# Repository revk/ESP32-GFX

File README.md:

# Simple SPI display controller

Provides simple tools to allow a screen buffer to be updated with text, boxes, etc.

Handles basic RGB for OLED/LCD RGB display, and simple mono for epaper.

Designed to allow for various SPI based display devices to be selected as part of config.

Note that the current state, graphics buffer, etc, are global, so only one display is supported.

- Includes scaled vector based font based on SAA5050 5x9 (Teletext/MODE7) with anti-aliasing.
- Includes scaled 7 segment (plus `.` and `:`), with anti-aliasing
- Includes simple box and line drawing

## Display types

### Solid colour (e-paper)

Displays with simple solid colour, such as black/white, black/red/white, etc, are handled quite simply with each pixel being one of the solid colours. The colour picked simply mapper from the RGB specified.

A simple dithering is applied on grey levels.

Anti-aliasing and alpha blending are not supported (top bit of alpha determines if plotted of not). As such italics is not recommended (text and 7 segment).

### Greyscale and colour

Displays with greyscale or colours allow antialiasing and alpha blending. A pixel can be set based on an RGB value - for greyscale this is mapped to a grey level.

Alpha blending is handled, mixing the new plotted pixel with the existing based on an alpha level.

Antialiasing is used for text, and 7 segment digits to improve quality, this will be added to other functions (line, circle, etc).

### Key functions

#### `gfx_init`

Sets up the display and options including all GPIOs and a number of flags.

#### `gfx_width` / `gfx_height` / `gfx_bpp`

Provide details of current display size and attriblues

#### `gfx_lock` / `gfx_unlock`

Call lock, then plot things, then unlock. Depending on the initial settings the display will be updated on unlock or on a background task (which locks while sending).

#### `gfx_foreground`/`gfx_background`

These set the current foreground and background to use. For text and 7 segment a solid background is set as a box first and then the text or 7 segment is plotted. This can be disabled by setting the same colour for foreground and background allowing plotting over the existing pixels with alpha blending. You can check current values with `gfx_f` and `gfx_b`.

#### `gfx_pixel_argb`

This set a pixel based on a 32 bit value (AARRGGBB), an alpha of 0xFF is plot, 0x00 is don't plot, otherwise alpha blend (non antialiasing displays simply test top bit of alpha to plot or not plot).

- `gfx_pixel` plots using current foreground colour width specified alpha
- `gfx_pixel_bg` plots using current background colour width specified alpha
- `gfx_pixel_rgb` plots specified colour (RRGGBB), same as alpha 0xFF
- `gfx_clear` plots a blend of current background and current foreground for whole display based on an alpha value
- `gfx_pixel_fb` plots a blend of current background and current foreground for a pixel based on an alpha value (if background/foreground same then does `gfx_pixel`)

#### `gfx_pos`

Sets current position and alignment for other functions. You can get current values `gf_x`, `gfx_y`, `gfx_a`.

#### `gfx_text` and `gfx_7seg`

These plot text or fixed digits. They have a number of flags and a based size. It plots at current position and alignment and moves to new position.

- `gfx_text` plots vector based text including a load of unicode characters - this allows newlines
- `gfx_7seg` plots digits, and `.` or `:` after a digit, and a number of letters than can be expressed using 7 segment display format

You can check size of text with `gfx_text_size` and `gfx_7seg_size`.

Note for text, a `size` of 0 plots a non anti-aliased size 1.

If using the `GFX_7SEG_SMALL_DOT` flag, a trailing `C` or `F` character is superscript (for temperatures).

There are various options including italic, dotty, blocky, etc.

#### `gfx_line`

A number of extra functions exist - these are being updated and new functions added.

#### `gfx_message`

This is a simple generic message display, typically used with a `message` command in various apps. The argument is a string with some special cases. The message is displayed centred from the top down, as several lines where lines are broken using a `/` character.

Lines can start with some characters within `[` and `]`, these include colour characters, e.g. `R` for red. A second colour character setting the background. A digit or digits sets the text size. You can also set flags for text (`_` for descenders, `|` for thin, `/` for italic).

Note: gfx_message calls gfx_lock/unlock.

### Some simple data tables

- `sin256` a table of sin() for 90 degrees (0-255) giving value 0-255
- `circle256` a table of x for y for a quarter circle 0-255 giving value 0-255

### Images

You can make use of the `lwpng` library for processing a png and calling `gfx_pixel_argb`. If you want to access the frame buffer `gfx_raw_w`, `gfx_raw_h` and `gfx_raw_b` allow access to the raw buffer - you will need to decode pixel values depending on `gfx_bpp` if you want to make a png.

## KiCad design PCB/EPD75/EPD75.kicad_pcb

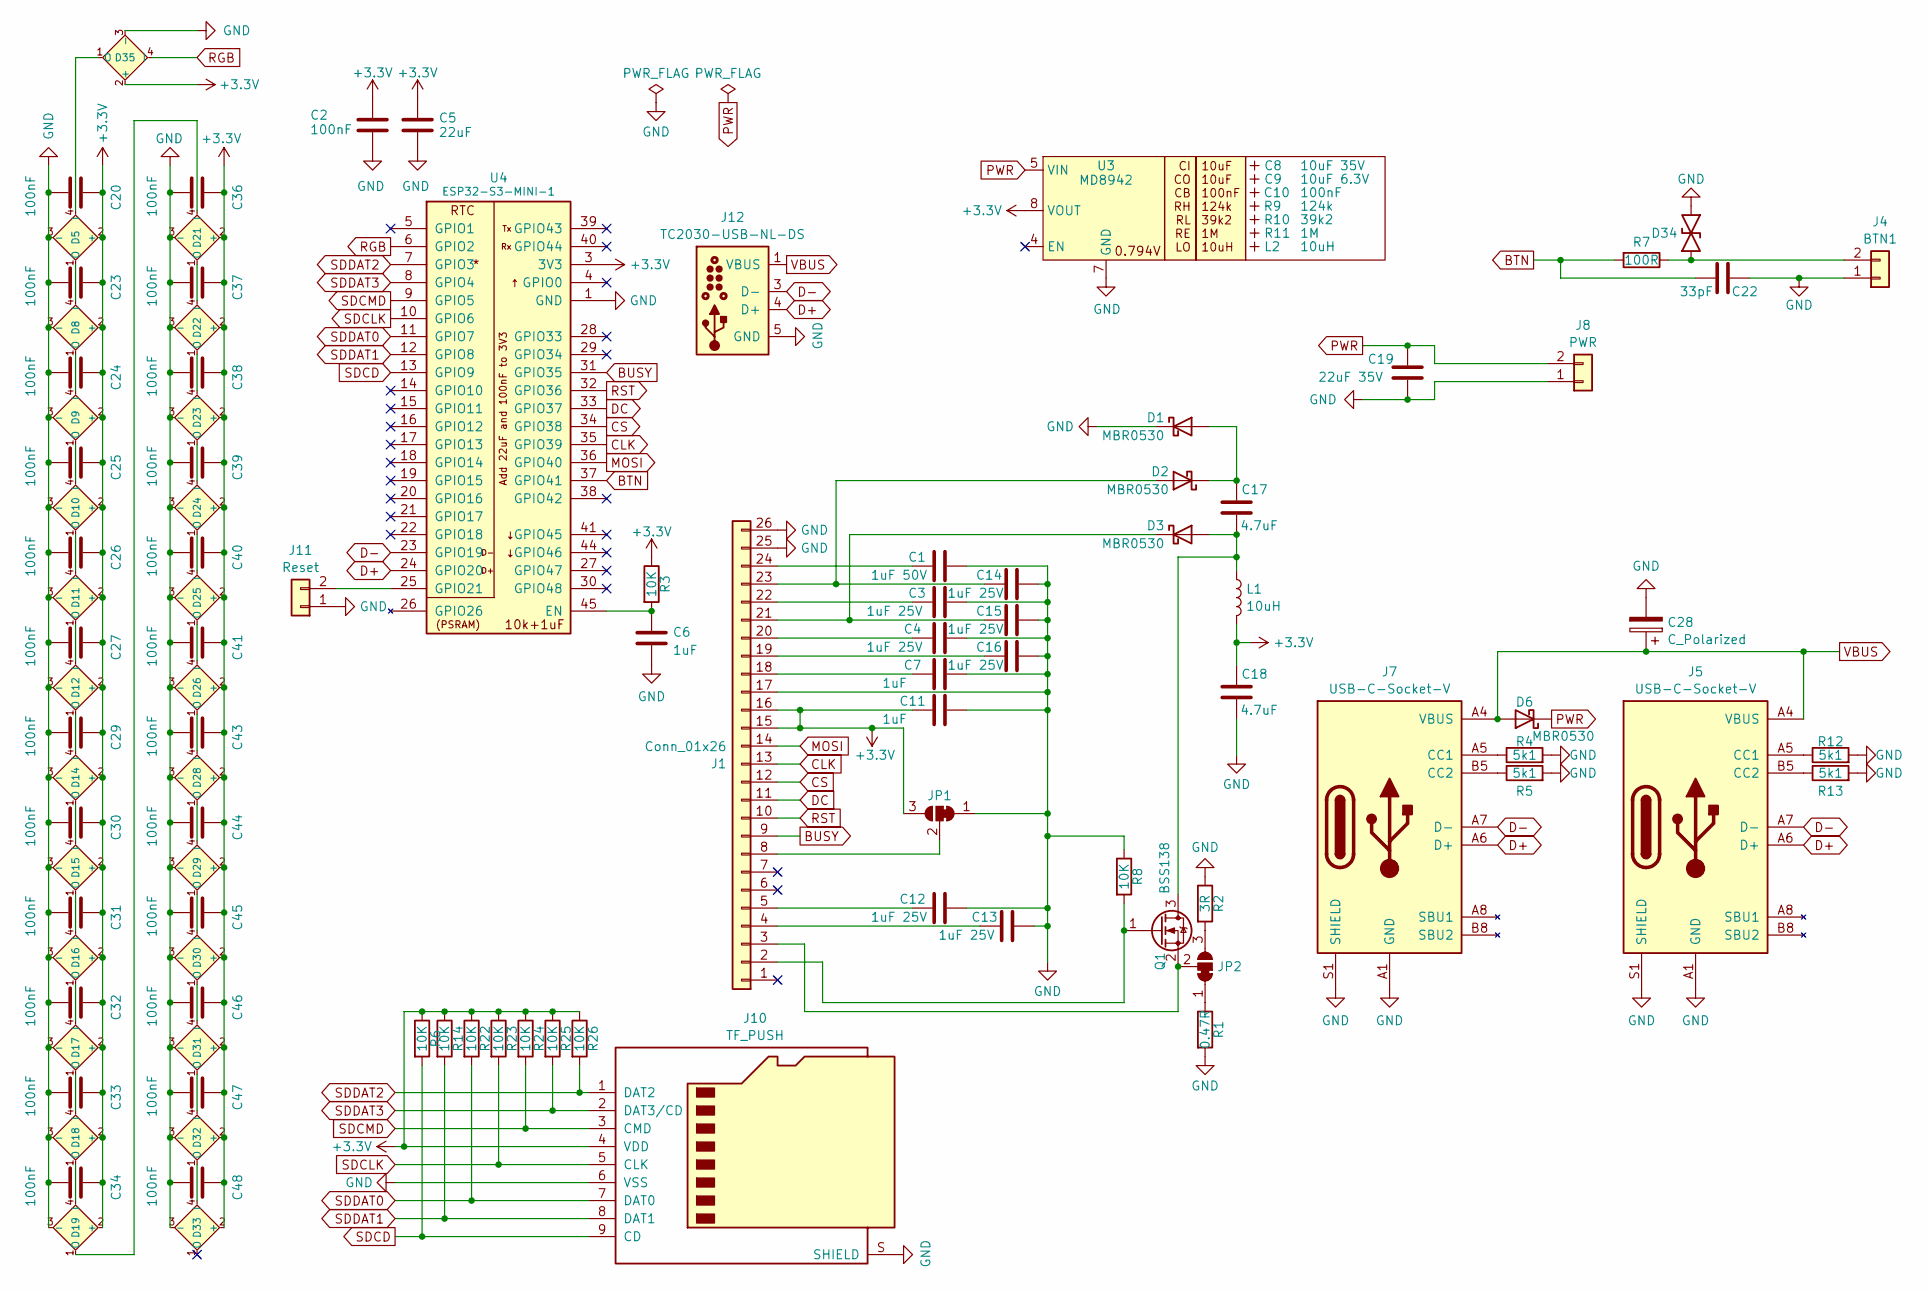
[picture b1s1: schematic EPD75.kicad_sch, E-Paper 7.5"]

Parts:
C1: 1uF 50V; C_0603
C2, C20, C23, C24, C25, C26, C27, C29, C30, C31, C32, C33, C34, C36, C37, C38, C39, C40, C41, C43, C44, C45, C46, C47, C48: 100nF; C_0402
C3, C4, C12, C13, C14, C15, C16: 1uF 25V; C_0402
C5: 22uF; C_0603
C6, C7, C11: 1uF; C_0402
C8: 10uF 35V; C_0603_; MPN C194427
C9: 10uF 6.3V; C_0603_; MPN C1691
C10: 100nF; C_0603_
C17, C18: 4.7uF; C_0402
C19: 22uF 35V; C_1210
C22: 33pF; C_0402
C28: C_Polarized; CP_EIA-7343-31_Kemet-D; MPN C106188
D1, D2, D3, D6: MBR0530; D_SOD-123; MPN C5204746
D5, D8, D9, D10, D11, D12, D14, D15, D16, D17, D18, D19, D21, D22, D23, D24, D25, D26, D28, D29, D30, D31, D32, D33, D35: XL-1010RGBC-WS2812B; MPN C5349953
D34: DFN1006-2L; MPN C5137770
J1: Conn_01x26; XUNPU-FPC-05FB-24PH20; MPN C2856831
J4: BTN1; WAGO-2060-452-998-404; MPN C2765055
J5, J7: USB-C-Socket-V; USB-C-Socket-H; MPN C709357
J8: PWR; WAGO-2060-452-998-404; MPN C2765055
J10: TF_PUSH; MPN C393941
J11: Reset; AA-Pad
J12: TC2030-USB-NL-DS; Tag-Connect_TC2030-IDC-NL_2x03_P1.27mm_Vertical
JP1, JP2: SolderJumper_3_Bridged12; SolderJumper3
L1: 10uH; L_4x4
L2: 10uH; L_4x4_
Q1: BSS138; SOT-23; MPN C2938375
R1: 0.47R; R_0402; MPN C2771738
R2: 3R; R_0402
R3, R6, R8, R14, R22, R23, R24, R25, R26: 10K; R_0402
R4, R5, R12, R13: 5k1; R_0402
R7: 100R; R_0402
R9: 124k; R_0402_; MPN C138062
R10: 39k2; R_0402_
R11: 1M; R_0402_
U3: MD8942; SOT-23-6-MD8942; MPN C2684786
U4: ESP32-S3-MINI-1; MPN C3013941

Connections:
+3.3V: C2.1, C5.1, C11.1, C18.2, C20.1, C23.1, C24.1, C25.1, C26.1, C27.1, C29.1, C30.1, C31.1, C32.1, C33.1, C34.1, C36.1, C37.1, C38.1, C39.1, C40.1, C41.1, C43.1, C44.1, C45.1, C46.1, C47.1, C48.1, D5.2 (+), D8.2 (+), D9.2 (+), D10.2 (+), D11.2 (+), D12.2 (+), D14.2 (+), D15.2 (+), D16.2 (+), D17.2 (+), D18.2 (+), D19.2 (+), D21.2 (+), D22.2 (+), D23.2 (+), D24.2 (+), D25.2 (+), D26.2 (+), D28.2 (+), D29.2 (+), D30.2 (+), D31.2 (+), D32.2 (+), D33.2 (+), D35.2 (+), J1.15, J1.16, J10.4 (VDD), JP1.3 (B), L1.2, R3.1, R6.1, R14.1, R22.1, R23.1, R24.1, R25.1, R26.1, U3.8 (VOUT), U4.3 (3V3)
BTN: C22.1, R7.2, U4.37 (GPIO41)
BUSY: J1.9, U4.31 (GPIO35)
CLK: J1.13, U4.35 (GPIO39)
CS: J1.12, U4.34 (GPIO38)
D+: J5.A6 (D+), J5.B6 (D+), J7.A6 (D+), J7.B6 (D+), J12.4 (D+), U4.24 (GPIO20)
D-: J5.A7 (D-), J5.B7 (D-), J7.A7 (D-), J7.B7 (D-), J12.3 (D-), U4.23 (GPIO19)
DC: J1.11, U4.33 (GPIO37)
GND: C1.2, C2.2, C3.2, C4.2, C5.2, C6.2, C7.2, C11.2, C12.2, C14.2, C15.2, C18.1, C19.2, C20.2, C22.2, C23.2, C24.2, C25.2, C26.2, C27.2, C28.2, C29.2, C30.2, C31.2, C32.2, C33.2, C34.2, C36.2, C37.2, C38.2, C39.2, C40.2, C41.2, C43.2, C44.2, C45.2, C46.2, C47.2, C48.2, D1.1 (K), D5.3 (-), D8.3 (-), D9.3 (-), D10.3 (-), D11.3 (-), D12.3 (-), D14.3 (-), D15.3 (-), D16.3 (-), D17.3 (-), D18.3 (-), D19.3 (-), D21.3 (-), D22.3 (-), D23.3 (-), D24.3 (-), D25.3 (-), D26.3 (-), D28.3 (-), D29.3 (-), D30.3 (-), D31.3 (-), D32.3 (-), D33.3 (-), D34.1, D35.3 (-), J1.17, J1.25, J1.26, J4.1, J5.A1 (GND), J5.A12 (GND), J5.B1 (GND), J5.B12 (GND), J5.S1 (SHIELD), J7.A1 (GND), J7.A12 (GND), J7.B1 (GND), J7.B12 (GND), J7.S1 (SHIELD), J8.1, J10.6 (VSS), J10.S (SHIELD), J11.1, J12.5 (GND), J12.6 (GND), JP1.1 (A), R1.2, R2.1, R4.2, R5.2, R8.1, R12.2, R13.2, U3.2 (GND), U3.7 (GND), U4.1 (GND), U4.2 (GND), U4.42 (GND), U4.43 (GND), U4.46 (GND), U4.47 (GND), U4.48 (GND), U4.49 (GND), U4.50 (GND), U4.51 (GND), U4.52 (GND), U4.53 (GND), U4.54 (GND), U4.55 (GND), U4.56 (GND), U4.57 (GND), U4.58 (GND), U4.59 (GND), U4.60 (GND), U4.61 (GND), U4.62 (GND), U4.63 (GND), U4.64 (GND), U4.65 (GND)
MOSI: J1.14, U4.36 (GPIO40)
unnamed: C17.2, D1.2 (A), D2.1 (K)
unnamed: C14.1, D2.2 (A), J1.23
unnamed: C17.1, D3.2 (A), L1.1, Q1.3 (D)
unnamed: C15.1, D3.1 (K), J1.21
unnamed: D5.1 (O), D8.4 (I)
unnamed: D8.1 (O), D9.4 (I)
unnamed: D9.1 (O), D10.4 (I)
unnamed: D10.1 (O), D11.4 (I)
unnamed: D11.1 (O), D12.4 (I)
unnamed: D12.1 (O), D14.4 (I)
unnamed: D14.1 (O), D15.4 (I)
unnamed: D15.1 (O), D16.4 (I)
unnamed: D16.1 (O), D17.4 (I)
unnamed: D17.1 (O), D18.4 (I)
unnamed: D18.1 (O), D19.4 (I)
unnamed: D19.1 (O), D21.4 (I)
unnamed: D21.1 (O), D22.4 (I)
unnamed: D22.1 (O), D23.4 (I)
unnamed: D23.1 (O), D24.4 (I)
unnamed: D24.1 (O), D25.4 (I)
unnamed: D25.1 (O), D26.4 (I)
unnamed: D26.1 (O), D28.4 (I)
unnamed: D28.1 (O), D29.4 (I)
unnamed: D29.1 (O), D30.4 (I)
unnamed: D30.1 (O), D31.4 (I)
unnamed: D31.1 (O), D32.4 (I)
unnamed: D32.1 (O), D33.4 (I)
unnamed: D5.4 (I), D35.1 (O)
unnamed: J1.2, Q1.1 (G), R8.2
unnamed: J1.3, JP2.2 (C), Q1.2 (S)
unnamed: C12.1, J1.5
unnamed: J1.8, JP1.2 (C)
unnamed: C7.1, J1.18
unnamed: C4.1, J1.20
unnamed: C1.1, J1.24
unnamed: D34.2, J4.2, R7.1
unnamed: J5.A5 (CC1), R12.1
unnamed: J5.B5 (CC2), R13.1
unnamed: J7.A5 (CC1), R4.1
unnamed: J7.B5 (CC2), R5.1
unnamed: J11.2, U4.25 (GPIO21)
unnamed: JP2.1 (A), R1.1
unnamed: JP2.3 (B), R2.2
unnamed: C6.1, R3.2, U4.45 (EN)
PWR: C19.1, D6.1 (K), J8.2, U3.5 (VIN)
RGB: D35.4 (I), U4.6 (GPIO2)
RST: J1.10, U4.32 (GPIO36)
SDCD: J10.9 (CD), R6.2, U4.13 (GPIO9)
SDCLK: J10.5 (CLK), R23.2, U4.10 (GPIO6)
SDCMD: J10.3 (CMD), R24.2, U4.9 (GPIO5)
SDDAT0: J10.7 (DAT0), R22.2, U4.11 (GPIO7)
SDDAT1: J10.8 (DAT1), R14.2, U4.12 (GPIO8)
SDDAT2: J10.1 (DAT2), R26.2, U4.7 (GPIO3)
SDDAT3: J10.2 (DAT3/CD), R25.2, U4.8 (GPIO4)
VBUS: C28.1, D6.2 (A), J5.A4 (VBUS), J5.A9 (VBUS), J5.B4 (VBUS), J5.B9 (VBUS), J7.A4 (VBUS), J7.A9 (VBUS), J7.B4 (VBUS), J7.B9 (VBUS), J12.1 (VBUS), J12.2 (VBUS)

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
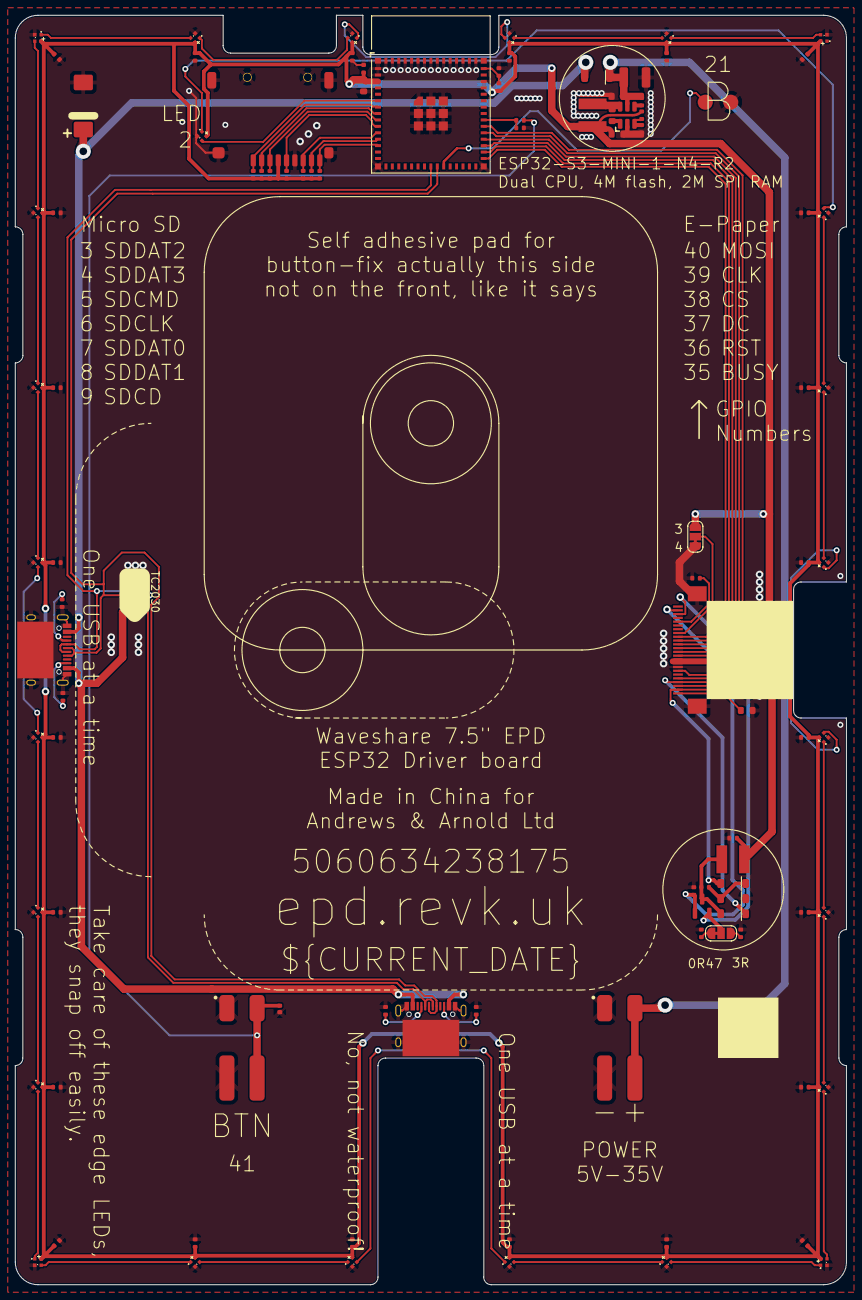
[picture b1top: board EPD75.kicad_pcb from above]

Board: 2 copper layers, 110.0 x 168.0 mm, 107 parts (0 on the bottom side), 66 nets.

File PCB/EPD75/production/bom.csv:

Designator,Footprint,Quantity,Value,LCSC Part #
C1,C_0603,1,1uF 50V,
C10,C_0603_,1,100nF,
"C11, C6, C7",C_0402,3,1uF,
"C12, C14, C15, C3, C4",C_0402,5,1uF 25V,
"C17, C18",C_0402,2,4.7uF,
C19,C_1210,1,22uF 35V,
"C2, C20, C23, C24, C25, C26, C27, C29, C30, C31, C32, C33, C34, C36, C37, C38, C39, C40, C41, C43, C44, C45, C46, C47, C48",C_0402,25,100nF,
C22,C_0402,1,33pF,
C28,CP_EIA-7343-31_Kemet-D,1,C_Polarized,C106188
C5,C_0603,1,22uF,
C8,C_0603_,1,10uF 35V,C194427
C9,C_0603_,1,10uF 6.3V,C1691
"D1, D2, D3, D6",D_SOD-123,4,MBR0530,C5204746
"D10, D11, D12, D14, D15, D16, D17, D18, D19, D21, D22, D23, D24, D25, D26, D28, D29, D30, D31, D32, D33, D35, D5, D8, D9",SMD1010,25,XL-1010RGBC-WS2812B,C5349953
D34,DFN1006-2L,1,~,C5137770
J1,XUNPU-FPC-05FB-24PH20,1,Conn_01x26,C2856831
J10,TF_PUSH,1,TF_PUSH,C393941
J4,WAGO-2060-452-998-404,1,BTN1,C2765055
"J5, J7",USB-C-Socket-H,2,USB-C-Socket-V,C709357
J8,WAGO-2060-452-998-404,1,PWR,C2765055
L1,L_4x4,1,10uH,
L2,L_4x4_,1,10uH,
Q1,SOT-23,1,BSS138,C2938375
R1,R_0402,1,0.47R,C2771738
R10,R_0402_,1,39k2,
R11,R_0402_,1,1M,
"R12, R13, R4, R5",R_0402,4,5k1,
"R14, R22, R23, R24, R25, R26, R3, R6, R8",R_0402,9,10K,
R2,R_0402,1,3R,
R7,R_0402,1,100R,
R9,R_0402_,1,124k,C138062
U3,SOT-23-6-MD8942,1,MD8942,C2684786
U4,ESP32-S3-MINI-1,1,ESP32-S3-MINI-1,C3013941

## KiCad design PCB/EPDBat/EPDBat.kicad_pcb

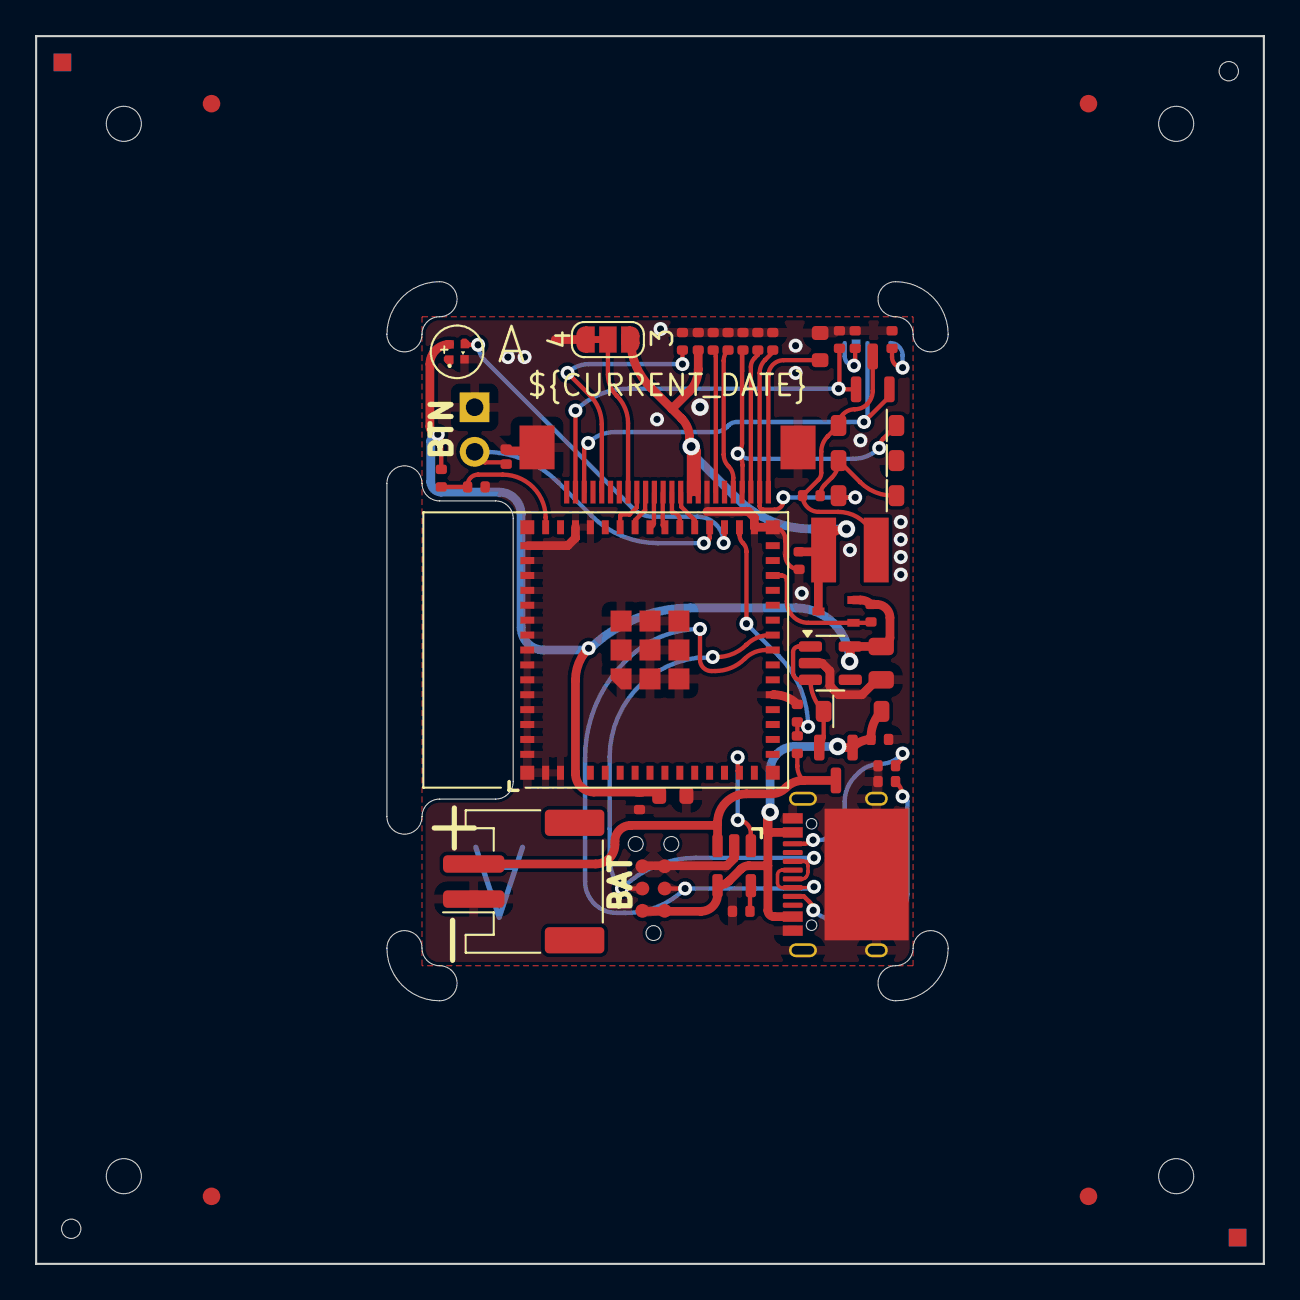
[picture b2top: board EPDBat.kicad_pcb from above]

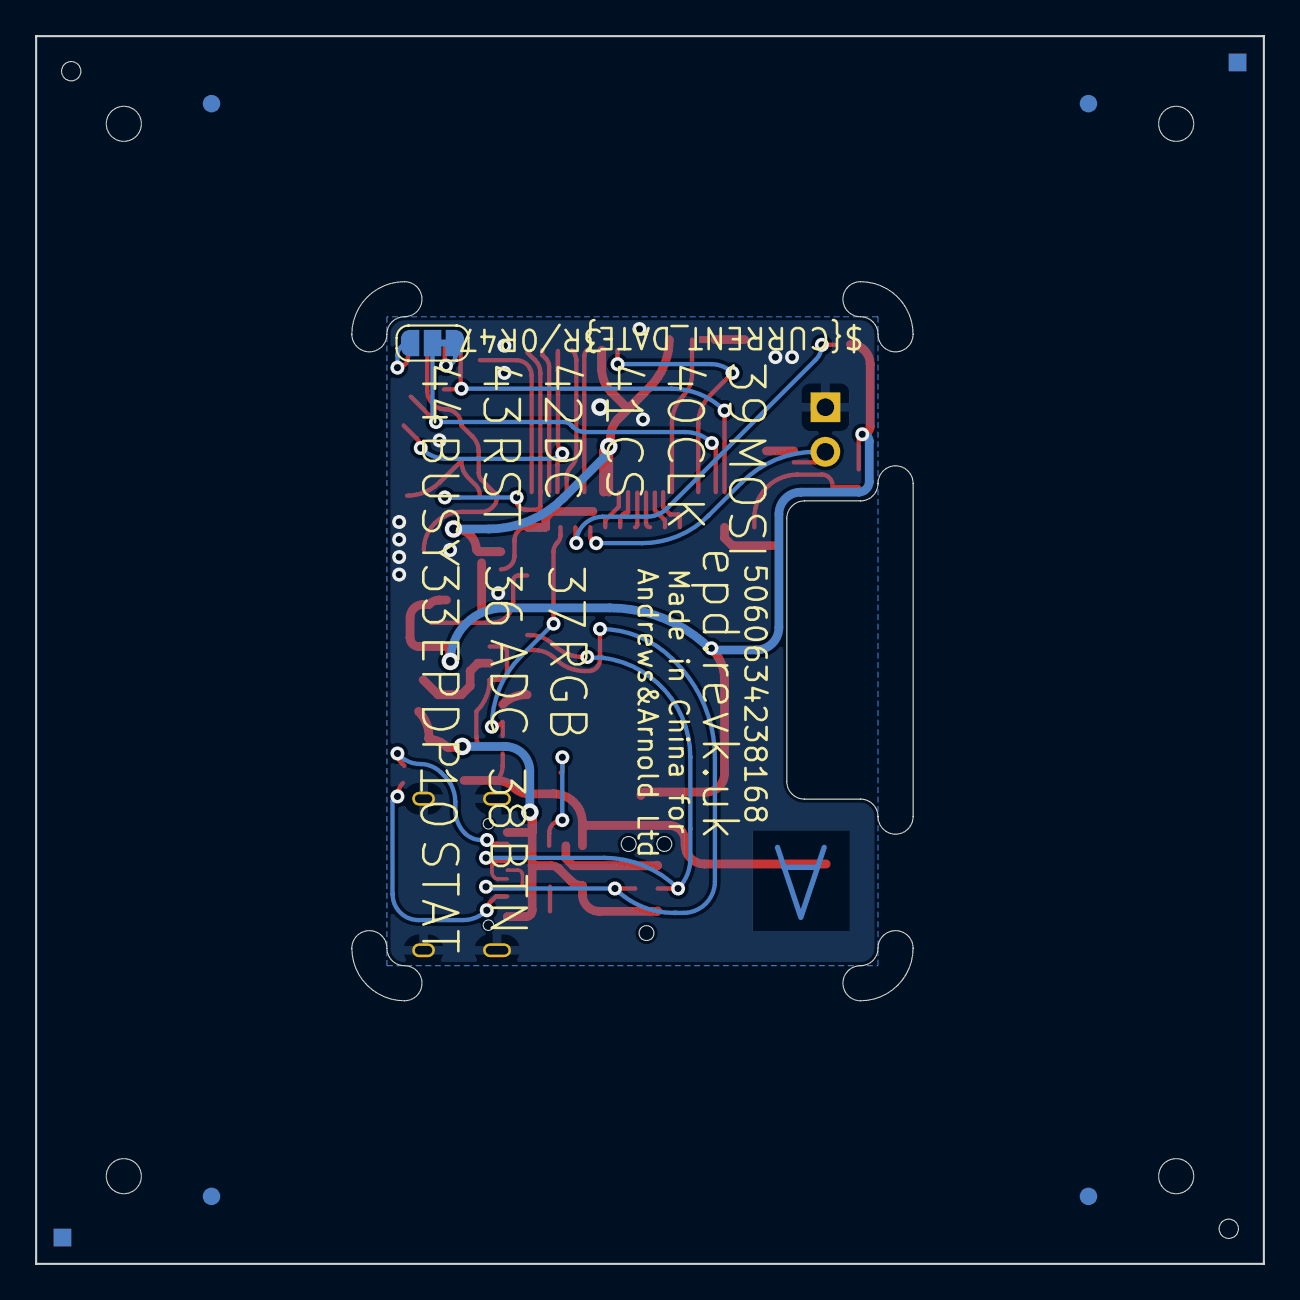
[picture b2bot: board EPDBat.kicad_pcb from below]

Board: 4 copper layers, 70.0 x 70.0 mm, 50 parts (3 on the bottom side), 37 nets.

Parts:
C1: 1uF 50V; C_0603
C2: 100nF; C_0402
C3, C4, C12, C14, C15: 1uF 25V; C_0402
C5: 22uF; C_0603
C6, C7, C11: 1uF; C_0402
C17, C18: 4.7uF; C_0402
C19: 4.7uF/50V; C_0805
D1, D2, D3, D5: MBR0530; D_SOD-123
D4: XL-1010RGBC-WS2812B; SMD1010
D6: DFN1006-2L
J1: Conn_01x26; XUNPU-FPC-05FB-24PH20
J4: Conn_01x02; PinHeader_1x02_P2.54mm_Vertical
J5: TC2030-USB-NL-DS; Tag-Connect_TC2030-IDC-NL_2x03_P1.27mm_Vertical
J7: USB-C-Socket-V; USB-C-Socket-H
J10: JST-PH-SM3-TB; JST_PH_S2B-PH-SM4-TB_1x02-1MP_P2.00mm_Horizontal
JP1, JP2: SolderJumper_3_Bridged12; SolderJumper3
L1: 10uH; L_4x4
PCB1: 70x70; PCB7070
Q1: BSS138; SOT-23
Q2: CJ2301; SOT-23
Q3: C179347; SOT-323_SC-70
R1: 0.47R; R_0402
R2: 3R; R_0402
R3, R8, R12, R13, R14: 10K; R_0402
R4, R5: 5k1; R_0402
R16, R17: 100K; R_0402
U1: TP4054; SOT-23-5
U2: ME6211C33M5G-N; SOT-23-5
U4: ESP32-S3-MINI-1
V1, V3, V4, V6: VCUT70N

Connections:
+3.3V: C2.1, C5.1, C19.1, D4.2 (+), Q3.2 (S), R3.1, R14.1, U2.5 (OUT), U4.3 (3V3)
ADC: R16.2, R17.1, U4.32 (GPIO36)
BTN: D6.2, J4.2, U4.34 (GPIO38)
BUSY: J1.9, U4.40 (GPIO44)
CLK: J1.13, U4.36 (GPIO40)
CS: J1.12, U4.37 (GPIO41)
D+: J5.4 (D+), J7.A6 (D+), J7.B6 (D+), U4.24 (GPIO20)
D-: J5.3 (D-), J7.A7 (D-), J7.B7 (D-), U4.23 (GPIO19)
DC: J1.11, U4.38 (GPIO42)
EPDP: Q3.1 (G), R14.2, U4.28 (GPIO33)
GND: C1.2, C2.2, C3.2, C4.2, C5.2, C6.2, C7.2, C11.2, C12.2, C14.2, C15.2, C18.1, C19.2, D1.1 (K), D4.3 (-), D6.1, J1.17, J1.25, J1.26, J4.1, J5.5 (GND), J5.6 (GND), J7.A1 (GND), J7.A12 (GND), J7.B1 (GND), J7.B12 (GND), J7.S1 (SHIELD), J10.1, JP2.1 (A), R1.2, R2.1, R4.2, R5.2, R8.1, R12.2, R13.1, R17.2, U1.2 (VSS), U2.2 (GND), U4.1 (GND), U4.2 (GND), U4.20 (GPIO16), U4.31 (GPIO35), U4.42 (GND), U4.43 (GND), U4.46 (GND), U4.47 (GND), U4.48 (GND), U4.49 (GND), U4.50 (GND), U4.51 (GND), U4.52 (GND), U4.53 (GND), U4.54 (GND), U4.55 (GND), U4.56 (GND), U4.57 (GND), U4.58 (GND), U4.59 (GND), U4.60 (GND), U4.61 (GND), U4.62 (GND), U4.63 (GND), U4.64 (GND), U4.65 (GND)
MOSI: J1.14, U4.35 (GPIO39)
unnamed: C17.2, D1.2 (A), D2.1 (K)
unnamed: C14.1, D2.2 (A), J1.23
unnamed: C17.1, D3.2 (A), L1.1, Q1.3 (D)
unnamed: C15.1, D3.1 (K), J1.21
unnamed: D5.1 (K), Q2.2 (S), U2.1 (IN), U2.3 (EN)
unnamed: J1.2, Q1.1 (G), R8.2
unnamed: J1.3, JP1.2 (C), Q1.2 (S)
unnamed: C12.1, J1.5
unnamed: J1.8, JP2.2 (C)
unnamed: C7.1, J1.18
unnamed: C4.1, J1.20
unnamed: C3.1, J1.22
unnamed: C1.1, J1.24
unnamed: J7.A5 (CC1), R4.1
unnamed: J7.B5 (CC2), R5.1
unnamed: JP1.1 (A), R2.2
unnamed: JP1.3 (B), R1.1
unnamed: R13.2, U1.5 (PROG)
unnamed: C6.1, R3.2, U4.45 (EN)
RGB: D4.4 (I), U4.33 (GPIO37)
RST: J1.10, U4.39 (GPIO43)
STAT: U1.1 (STAT), U4.14 (GPIO10)
VBAT: J10.2, Q2.3 (D), R16.1, U1.3 (VBAT)
VBUS: D5.2 (A), J5.1 (VBUS), J5.2 (VBUS), J7.A4 (VBUS), J7.A9 (VBUS), J7.B4 (VBUS), J7.B9 (VBUS), Q2.1 (G), R12.1, U1.4 (VDD)
VEPD: C11.1, C18.2, J1.15, J1.16, JP2.3 (B), L1.2, Q3.3 (D)

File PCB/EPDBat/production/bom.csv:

Designator,Footprint,Quantity,Value,LCSC Part #
C1,C_0603,1,1uF 50V,
"C11, C6, C7",C_0402,3,1uF,
"C12, C14, C15, C3, C4",C_0402,5,1uF 25V,
"C17, C18",C_0402,2,4.7uF,
C19,C_0805,1,4.7uF/50V,
C2,C_0402,1,100nF,
C5,C_0603,1,22uF,
"D1, D2, D3, D5",D_SOD-123,4,MBR0530,
D4,SMD1010,1,XL-1010RGBC-WS2812B,C5349953
D6,DFN1006-2L,1,~,C5137770
J1,XUNPU-FPC-05FB-24PH20,1,Conn_01x26,C2856831
J10,JST_PH_S2B-PH-SM4-TB_1x02-1MP_P2.00mm_Horizontal,1,JST-PH-SM3-TB,C295747
J4,PinHeader_1x02_P2.54mm_Vertical,1,Conn_01x02,
J7,USB-C-Socket-H,1,USB-C-Socket-V,C709357
L1,L_4x4,1,10uH,
Q1,SOT-23,1,BSS138,C2938375
Q2,SOT-23,1,CJ2301,C5224170
Q3,SOT-323_SC-70,1,C179347,C179347
R1,R_0402,1,0.47R,
"R12, R13, R14, R3, R8",R_0402,5,10K,
"R16, R17",R_0402,2,100K,
R2,R_0402,1,3R,
"R4, R5",R_0402,2,5k1,
U1,SOT-23-5,1,TP4054,C668215
U2,SOT-23-5,1,ME6211C33M5G-N,C82942
U4,ESP32-S3-MINI-1,1,ESP32-S3-MINI-1,C3013941

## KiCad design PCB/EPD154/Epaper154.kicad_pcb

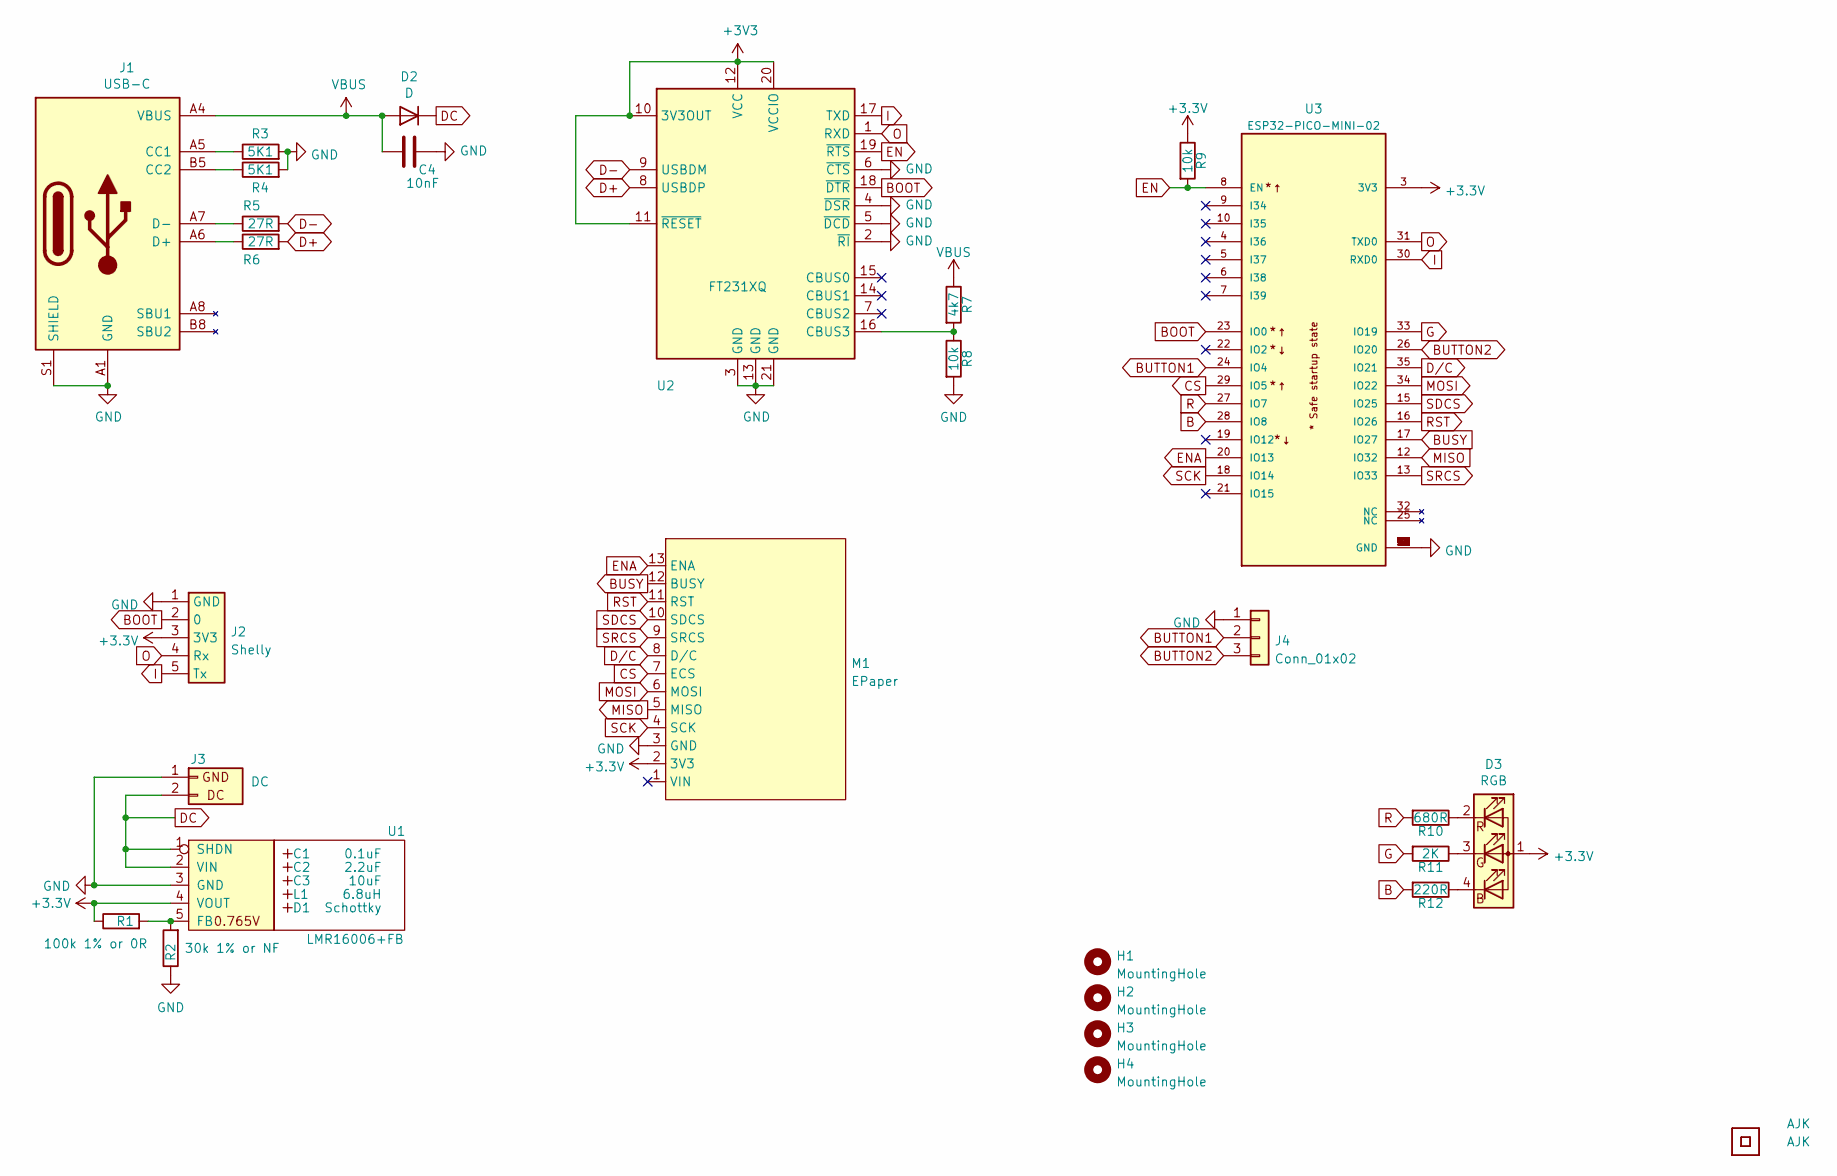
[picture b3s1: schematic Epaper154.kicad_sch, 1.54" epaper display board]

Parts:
C1: 0.1uF; Hidden
C2: 2.2uF; Hidden
C3: 10uF; Hidden
C4: 10nF; C_0603
D1: Schottky; Hidden; Part No CD1206-B2100
D2: D; D_1206
D3: RGB; LED-RGB-1.6x1.6
H1, H2, H3, H4: MountingHole; Hole-2.5mm
J1: USB-C; USC16-TR-Round
J2: Shelly
J3: DC; Molex_MiniSPOX_H2RA
J4: Conn_01x02; Molex_MiniSPOX_H3RA
L1: 6.8uH; Hidden; Part No TYA4020
Logo1, Logo2: AJK
M1: EPaper; PinHeader_1x13_P2.54mm_Vertical
R1: 100k 1% or 0R; R_0603
R2: 30k 1% or NF; R_0603
R3, R4: 5K1; R_0603
R5, R6: 27R; R_0603
R7: 4k7; R_0603
R8, R9: 10k; R_0603
R10: 680R; R_0603
R11: 2K; R_0603
R12: 220R; R_0603
U1: LMR16006+FB; RegulatorBlockFB; Part No LMR16006YQ3
U2: FT231XQ; QFN-20-1EP_4x4mm_P0.5mm_EP2.5x2.5mm
U3: ESP32-PICO-MINI-02; PARTREV v1.0
U4: QR; QR-GFX

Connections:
B: R12.2, U3.28 (IO8)
BOOT: J2.2 (0), U2.18 (~DTR), U3.23 (IO0)
BUSY: M1.12 (BUSY), U3.17 (IO27)
BUTTON1: J4.2, U3.24 (IO4)
BUTTON2: J4.3, U3.26 (IO20)
CS: M1.7 (ECS), U3.29 (IO5)
D+: R6.2, U2.8 (USBDP)
D-: R5.2, U2.9 (USBDM)
DC: D2.1 (K), J3.2 (DC), U1.1 (SHDN), U1.2 (VIN)
D/C: M1.8 (D/C), U3.35 (IO21)
EN: R9.2, U2.19 (~RTS), U3.8 (EN)
ENA: M1.13 (ENA), U3.20 (IO13)
G: R11.2, U3.33 (IO19)
GND: C4.1, J1.A1 (GND), J1.A12 (GND), J1.B1 (GND), J1.B12 (GND), J1.S1 (SHIELD), J2.1 (GND), J3.1 (GND), J4.1, M1.3 (GND), R2.1, R3.2, R4.2, R8.2, U1.3 (GND), U2.2 (~RI), U2.3 (GND), U2.4 (~DSR), U2.5 (~DCD), U2.6 (~CTS), U2.13 (GND), U2.21 (GND), U3.1 (GND), U3.2 (GND), U3.11 (GND), U3.14 (GND), U3.36 (GND), U3.37 (GND), U3.38 (GND), U3.39 (GND), U3.40 (GND), U3.41 (GND), U3.42 (GND), U3.43 (GND), U3.44 (GND), U3.45 (GND), U3.46 (GND), U3.47 (GND), U3.48 (GND), U3.49 (GND), U3.50 (GND), U3.51 (GND), U3.52 (GND), U3.53 (GND)
I: J2.5 (Tx), U2.17 (TXD), U3.30 (RXD0)
MISO: M1.5 (MISO), U3.12 (IO32)
MOSI: M1.6 (MOSI), U3.34 (IO22)
unnamed: D3.2 (RK), R10.1
unnamed: D3.3 (GK), R11.1
unnamed: D3.4 (BK), R12.1
unnamed: J1.A5 (CC1), R3.1
unnamed: J1.A6 (D+), J1.B6 (D+), R6.1
unnamed: J1.A7 (D-), J1.B7 (D-), R5.1
unnamed: J1.B5 (CC2), R4.1
unnamed: R1.2, R2.2, U1.5 (FB)
unnamed: R7.2, R8.1, U2.16 (CBUS3)
O: J2.4 (Rx), U2.1 (RXD), U3.31 (TXD0)
R: R10.2, U3.27 (IO7)
RST: M1.11 (RST), U3.16 (IO26)
SCK: M1.4 (SCK), U3.18 (IO14)
SDCS: M1.10 (SDCS), U3.15 (IO25)
SRCS: M1.9 (SRCS), U3.13 (IO33)
VBUS: C4.2, D2.2 (A), J1.A4 (VBUS), J1.A9 (VBUS), J1.B4 (VBUS), J1.B9 (VBUS), R7.1

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
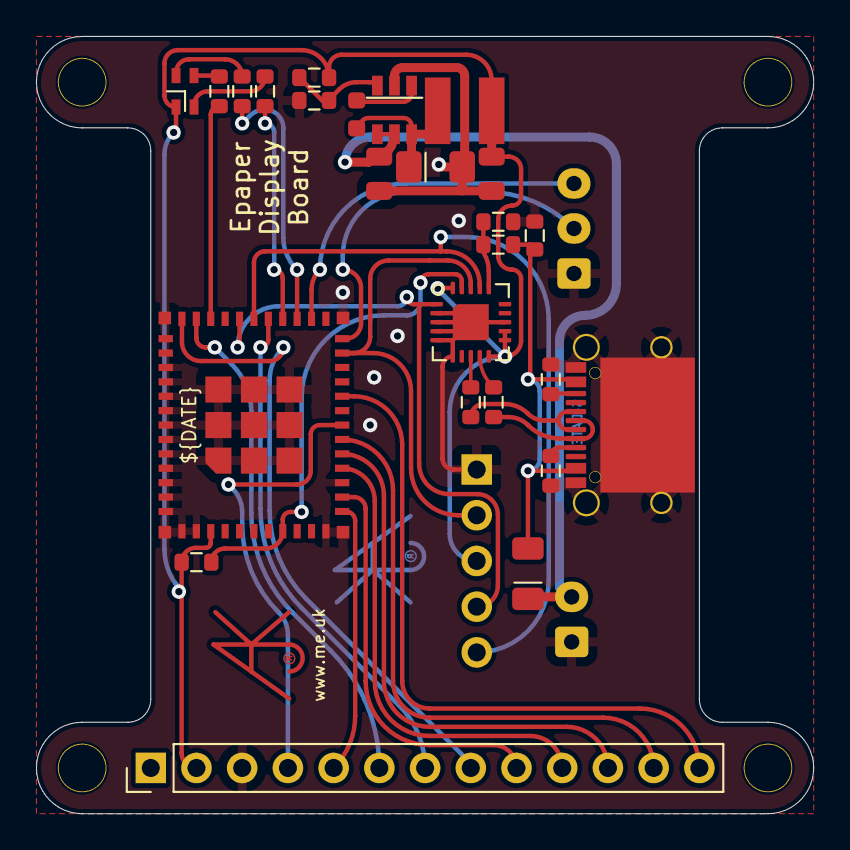
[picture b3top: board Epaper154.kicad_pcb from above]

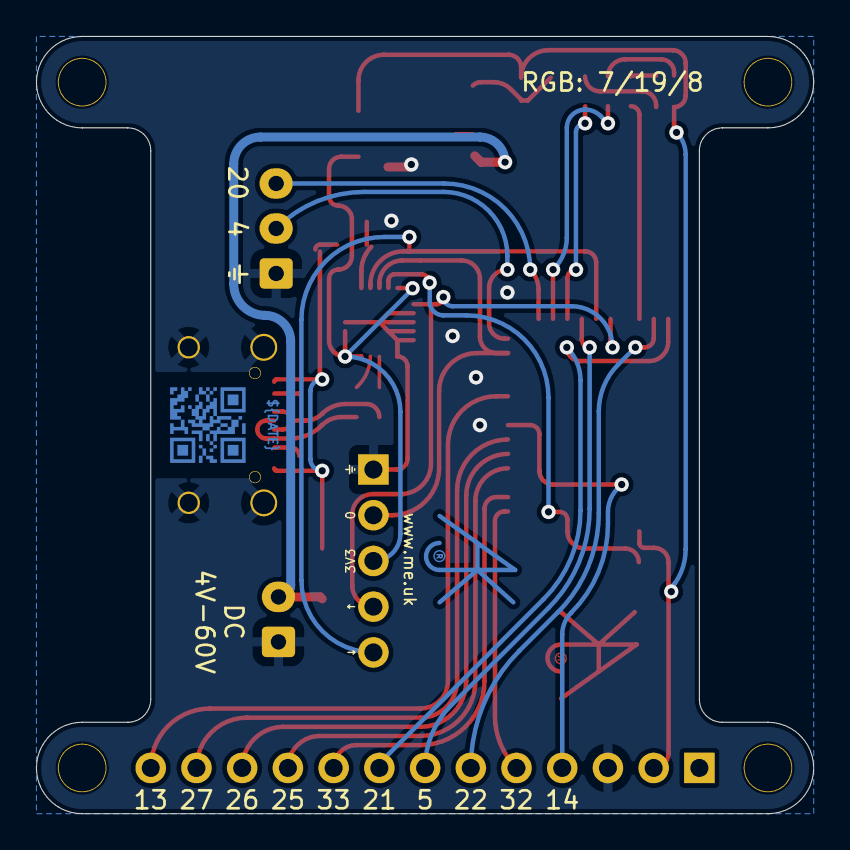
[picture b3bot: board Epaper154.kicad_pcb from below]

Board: 2 copper layers, 43.2 x 43.2 mm, 35 parts (3 on the bottom side), 34 nets.

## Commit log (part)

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2025-03-16 testing
2025-03-16 Secondary power for e-paper with control.
2025-03-17 Reworked vector
2025-03-20 Moved PCBs to EPD project
2025-03-21 TSE setting
2025-03-21 Testring
2025-03-21 epd.slow
2025-03-21 Tidy
2025-03-21 tweak
2025-03-21 defaults
2025-03-21 more settings
2025-03-21 deep sleep
2025-03-22 larger text
2025-04-03 improve 7seg
2025-04-07 testing new vector code
2025-04-07 Dropped the non vector, and the font size 0 logic
2025-04-08 uint16_t unicode
2025-04-08 Tidy script
2025-04-08 New 7 seg packing logic
2025-04-08 New 7 seg logic
2025-04-08 Bigger
2025-04-08 Adjusted size
2025-04-08 Adjust
2025-04-08 test
2025-04-09 Reworked vector font to be run length based for efficiency, especially with antialiased text
2025-04-09 7seg using new run length handling for alti-aliasing
2025-04-09 Italic
2025-04-10 LCD24
2025-04-10 Seems to work, need to test colour next
2025-04-10 Fix right hand side anti aliasing
2025-04-10 pixel colour plot
2025-04-10 mask options
2025-04-11 Some cleanup - needs colour logic fix
2025-04-11 Not needed any more
2025-04-11 README
2025-04-11 Reworked and documented pixel plotting and alpha logic
2025-04-11 Hardware flips logic...
2025-04-12 Spacing
2025-04-12 LCD2
2025-04-12 gfx_pixel_fg
2025-04-12 gfx_pixel_fb
2025-04-12 dither
2025-04-14 Simpler
2025-04-14 Updated to half pixel units
2025-04-15 Dummy
2025-04-15 func
2025-04-15 Functions for circle, sin, cos, testing
2025-04-15 New circle
2025-04-15 OK circle and line not doing anti-aliasing yet
2025-04-15 circle working now, next is line
2025-04-15 lines
2025-04-15 Line fix
2025-04-16 Clean up edge cases
2025-04-16 comment
2025-04-17 C/F 7seg suffix logic
2025-04-18 Faster sin/circle functions, and more precision, and better scaling (interpolation)
2025-04-19 Blocky and dotty text
2025-04-21 Changes to low level pixel plots to plot horizontal runs so as to fit in with the text and 7seg and other plotting logic being horizontal runs.
2025-04-21 D'Oh
2025-04-22 More dither
2025-04-27 gfx_blend
2025-04-27 Added 2 subscript
2025-04-27 font
2025-04-28 Grid
2025-04-28 Fix 7 seg sizing
2025-05-16 error
2025-05-16 mallocspi
2025-05-17 Allow ---.-C etc
2025-05-27 document gfx_message()
2025-05-27 Clarify
2025-05-27 non gfx gfx_message
